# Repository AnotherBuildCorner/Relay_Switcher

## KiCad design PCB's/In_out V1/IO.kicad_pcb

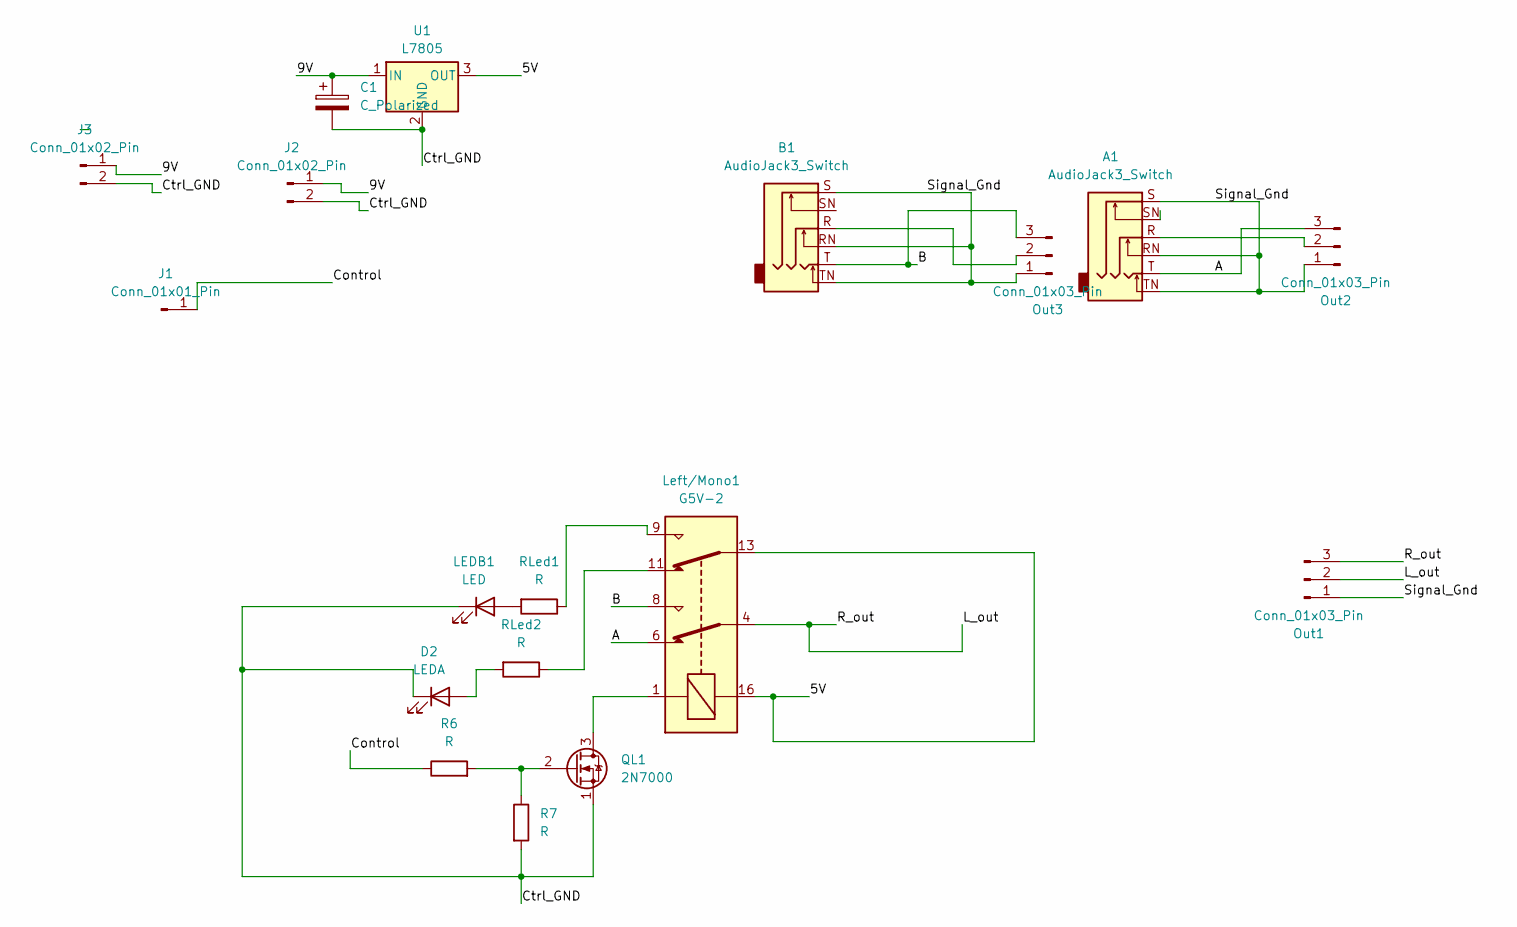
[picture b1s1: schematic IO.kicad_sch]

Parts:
A1: AudioJack3_Switch; Jack_6.35mm_Neutrik_NMJ6HFD3_Horizontal
B1: AudioJack3_Switch; Jack_6.35mm_Neutrik_NMJ6HFD3_Horizontal
C1: C_Polarized; CP_Radial_D10.0mm_P3.50mm
D2: LEDA; LED_D5.0mm
J1: Conn_01x01_Pin; PinHeader_1x01_P2.54mm_Vertical
J2, J3: Conn_01x02_Pin; PinHeader_2x01_P2.54mm_Vertical
LEDB1: LED; LED_D5.0mm
Left/Mono1: G5V-2; Relay_DPDT_Omron_G5V-2
Out1, Out2, Out3: Conn_01x03_Pin; PinHeader_1x03_P2.54mm_Vertical
QL1: 2N7000; TO-92_Inline
R6, R7: R; R_Axial_DIN0207_L6.3mm_D2.5mm_P10.16mm_Horizontal
RLed1, RLed2: R; R_Axial_DIN0207_L6.3mm_D2.5mm_P10.16mm_Horizontal
U1: L7805; TO-220-3_Vertical

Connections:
/5V: Left/Mono1.13, Left/Mono1.16, U1.3 (OUT)
/9V: C1.1, J2.1, J3.1, U1.1 (IN)
/A: A1.T, Left/Mono1.6, Out2.3
/B: B1.T, Left/Mono1.8, Out3.3
/Control: J1.1, R6.1
/Ctrl_GND: C1.2, D2.1 (K), J2.2, J3.2, LEDB1.1 (K), QL1.1 (S), R7.2, U1.2 (GND)
/L_out: Left/Mono1.4, Out1.2, Out1.3
/Signal_Gnd: A1.RN, A1.S, A1.TN, B1.RN, B1.S, B1.TN, Out1.1, Out2.1, Out3.1
unnamed: D2.2 (A), RLed2.2
unnamed: LEDB1.2 (A), RLed1.2
unnamed: Left/Mono1.9, RLed1.1
unnamed: Left/Mono1.11, RLed2.1
unnamed: A1.R, Out2.2
unnamed: B1.R, Out3.2
unnamed: Left/Mono1.1, QL1.3 (D)
unnamed: QL1.2 (G), R6.2, R7.1

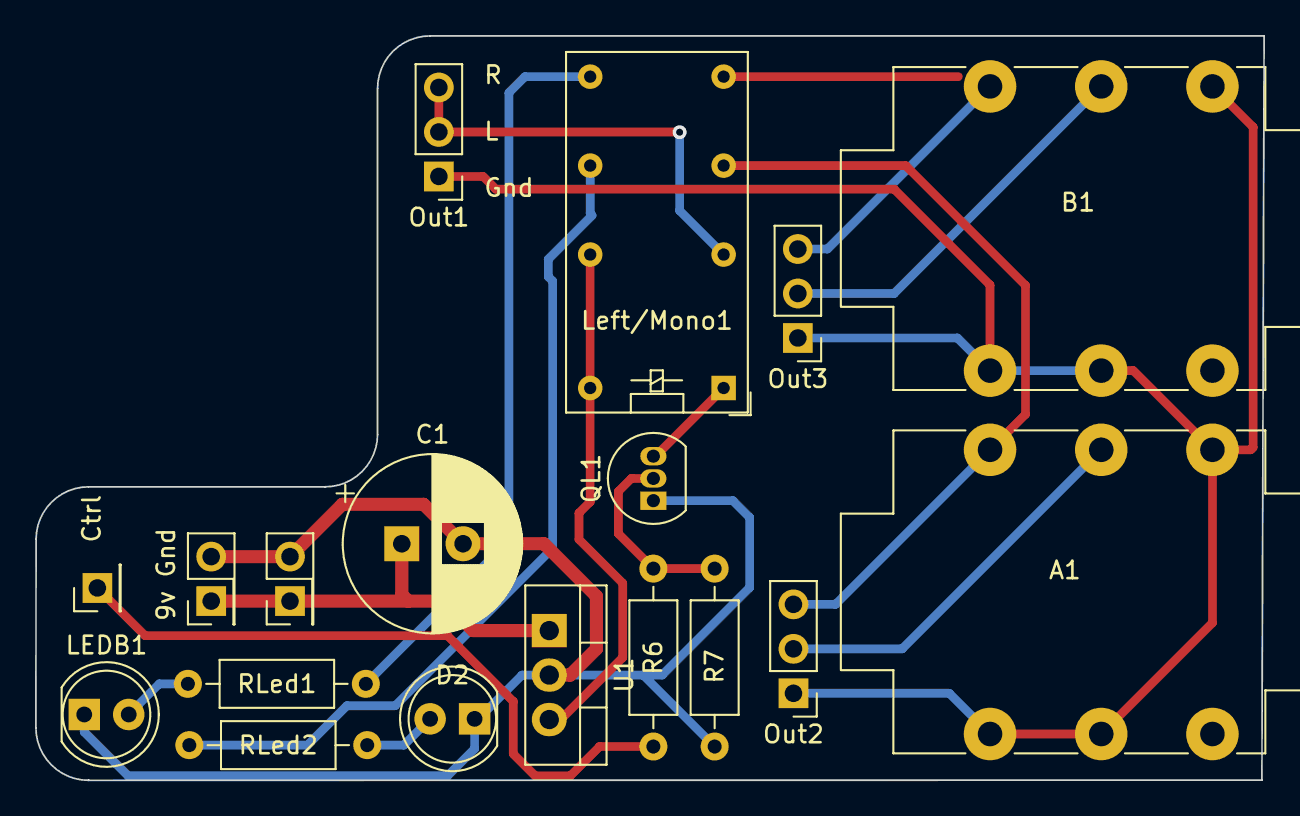
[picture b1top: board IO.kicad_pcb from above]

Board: 2 copper layers, 70.1 x 42.5 mm, 18 parts (0 on the bottom side), 16 nets.

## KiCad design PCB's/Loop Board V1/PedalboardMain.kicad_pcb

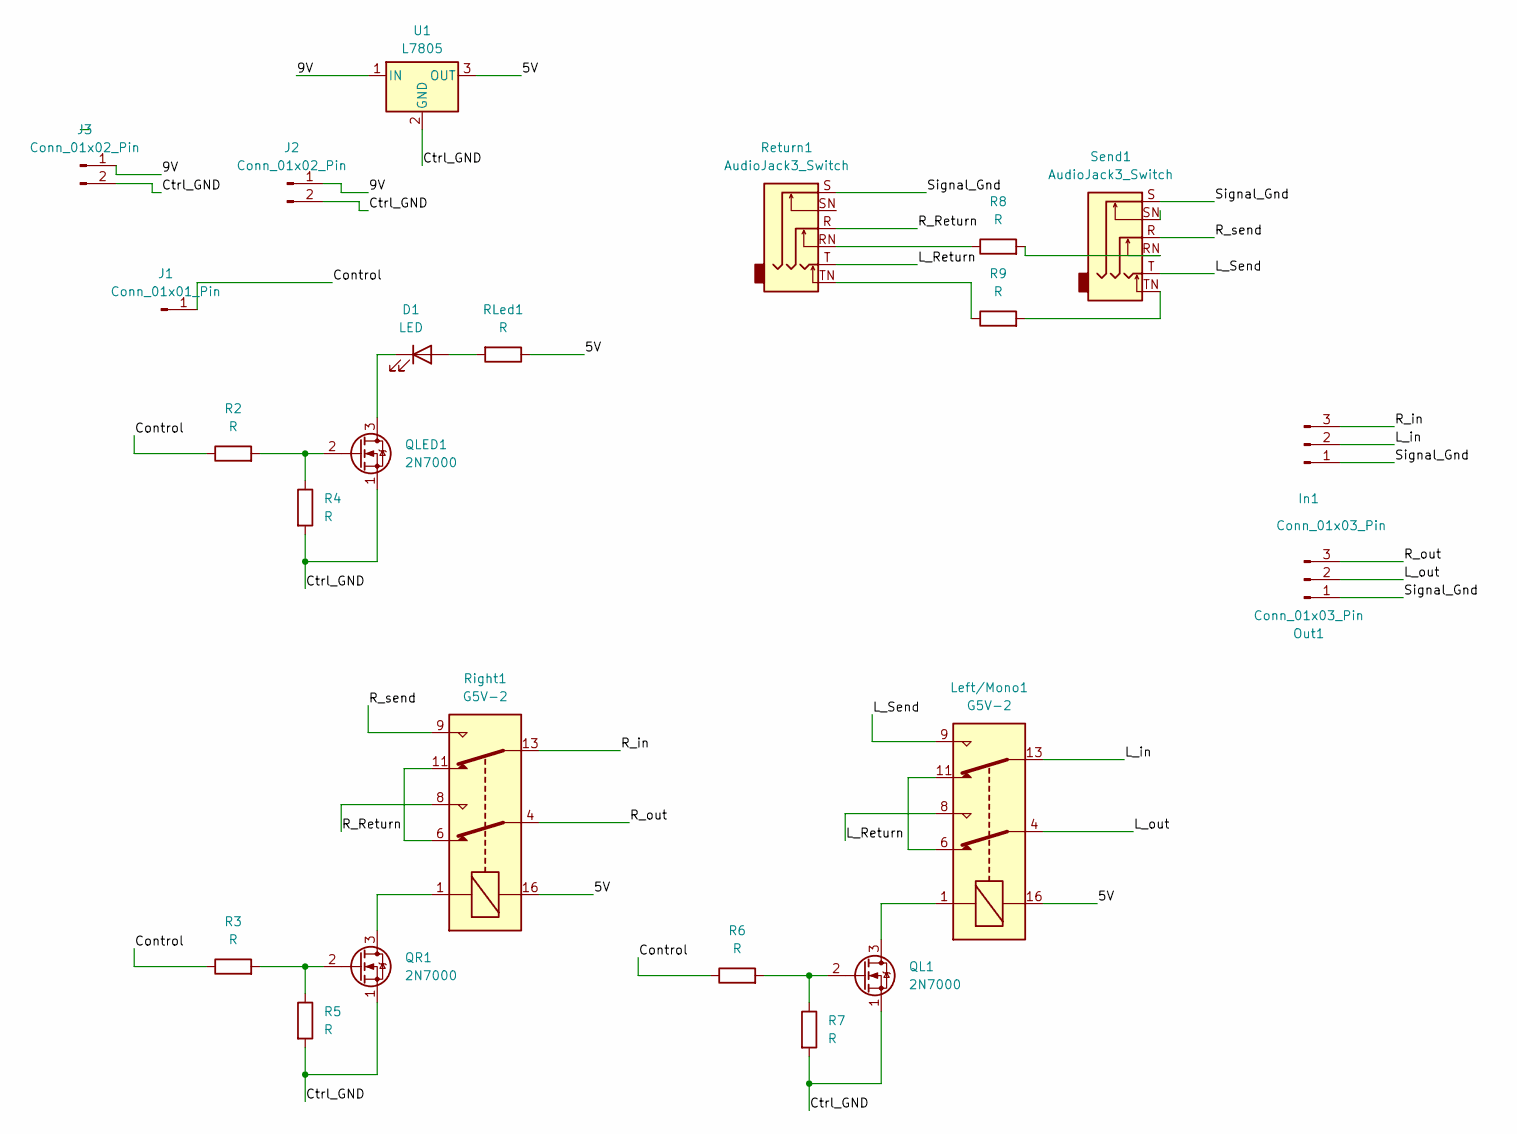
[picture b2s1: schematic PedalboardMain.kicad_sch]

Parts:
D1: LED; LED_D5.0mm
In1: Conn_01x03_Pin; PinHeader_1x03_P2.54mm_Vertical
J1: Conn_01x01_Pin; PinHeader_1x01_P2.54mm_Vertical
J2, J3: Conn_01x02_Pin; PinHeader_2x01_P2.54mm_Vertical
Left/Mono1: G5V-2; Relay_DPDT_Omron_G5V-2
Out1: Conn_01x03_Pin; PinHeader_1x03_P2.54mm_Vertical
QL1: 2N7000; TO-92_Inline
QLED1: 2N7000; TO-92_Inline
QR1: 2N7000; TO-92_Inline
R2, R3, R4, R5, R6, R7: R; R_Axial_DIN0207_L6.3mm_D2.5mm_P10.16mm_Horizontal
R8, R9: R; R_0201_0603Metric
RLed1: R; R_Axial_DIN0207_L6.3mm_D2.5mm_P10.16mm_Horizontal
Return1: AudioJack3_Switch; Jack_6.35mm_Neutrik_NMJ6HFD3_Horizontal
Right1: G5V-2; Relay_DPDT_Omron_G5V-2
Send1: AudioJack3_Switch; Jack_6.35mm_Neutrik_NMJ6HFD3_Horizontal
U1: L7805; TO-220-3_Vertical

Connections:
/5V: Left/Mono1.16, RLed1.1, Right1.16, U1.3 (OUT)
/9V: J2.1, J3.1, U1.1 (IN)
/Control: J1.1, R2.1, R3.1, R6.1
/Ctrl_GND: J2.2, J3.2, QL1.1 (S), QLED1.1 (S), QR1.1 (S), R4.2, R5.2, R7.2, U1.2 (GND)
/L_Return: Left/Mono1.8, Return1.T
/L_Send: Left/Mono1.9, Send1.T
/L_in: In1.2, Left/Mono1.13
/L_out: Left/Mono1.4, Out1.2
/R_Return: Return1.R, Right1.8
/R_in: In1.3, Right1.13
/R_out: Out1.3, Right1.4
/R_send: Right1.9, Send1.R
/Signal_Gnd: In1.1, Out1.1, Return1.S, Send1.S
unnamed: D1.2 (A), RLed1.2
unnamed: D1.1 (K), QLED1.3 (D)
unnamed: Left/Mono1.6, Left/Mono1.11
unnamed: Left/Mono1.1, QL1.3 (D)
unnamed: QL1.2 (G), R6.2, R7.1
unnamed: QLED1.2 (G), R2.2, R4.1
unnamed: QR1.3 (D), Right1.1
unnamed: QR1.2 (G), R3.2, R5.1
unnamed: R8.1, Return1.RN
unnamed: R8.2, Send1.RN
unnamed: R9.1, Return1.TN
unnamed: R9.2, Send1.TN
unnamed: Right1.6, Right1.11

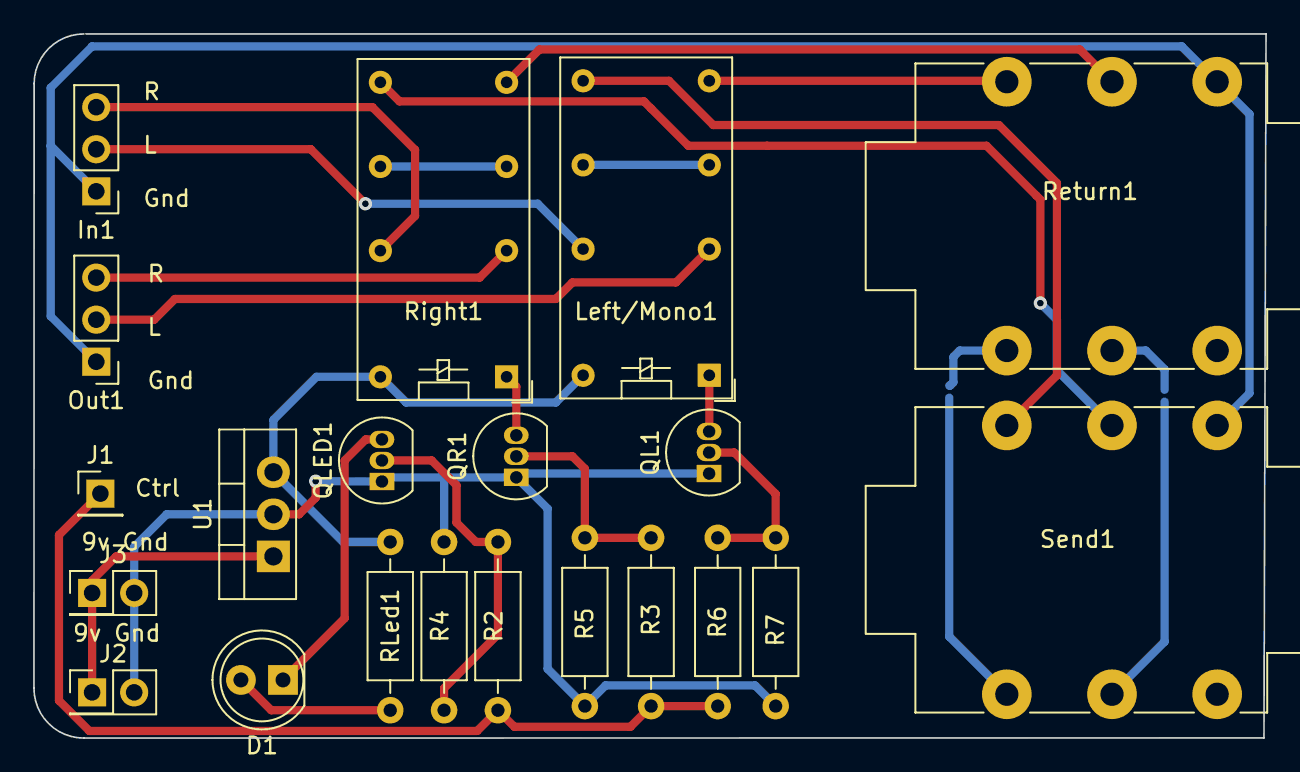
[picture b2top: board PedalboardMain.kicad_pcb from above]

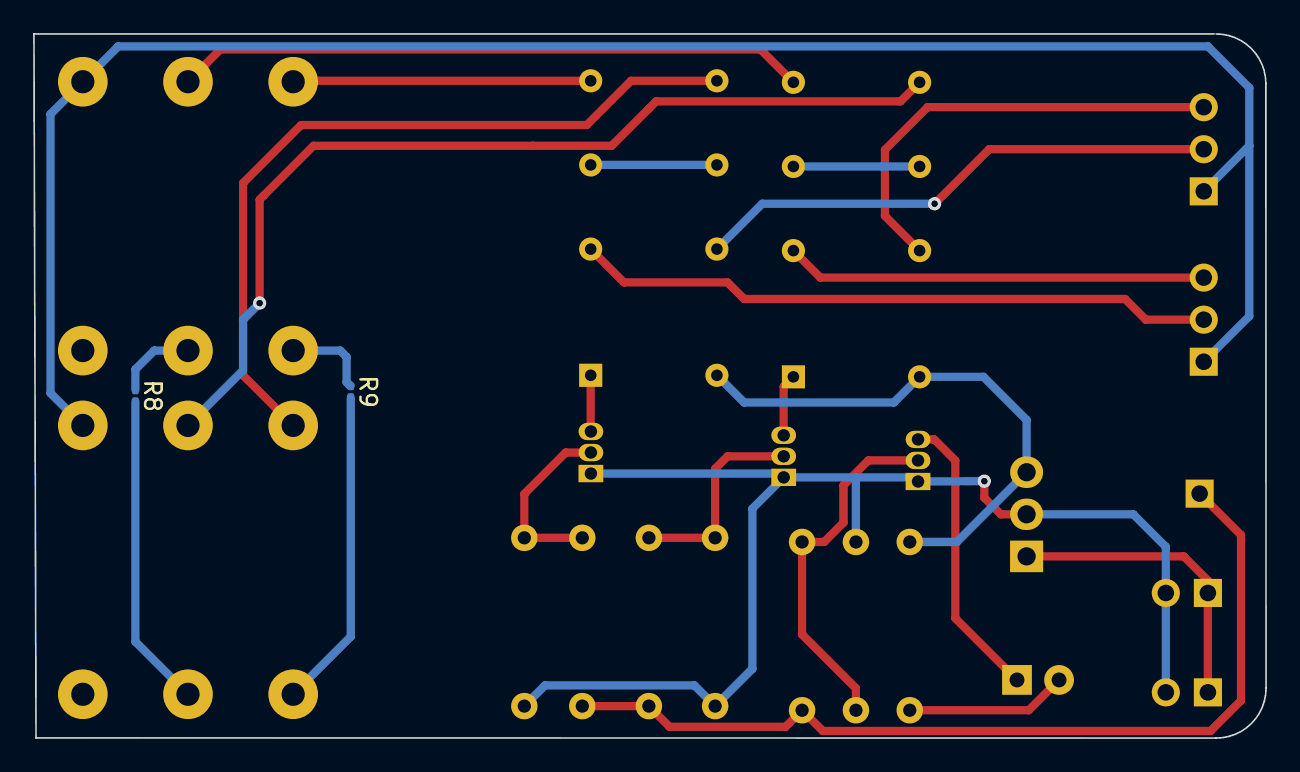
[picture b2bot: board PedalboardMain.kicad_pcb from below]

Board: 2 copper layers, 74.4 x 42.5 mm, 23 parts (2 on the bottom side), 26 nets.

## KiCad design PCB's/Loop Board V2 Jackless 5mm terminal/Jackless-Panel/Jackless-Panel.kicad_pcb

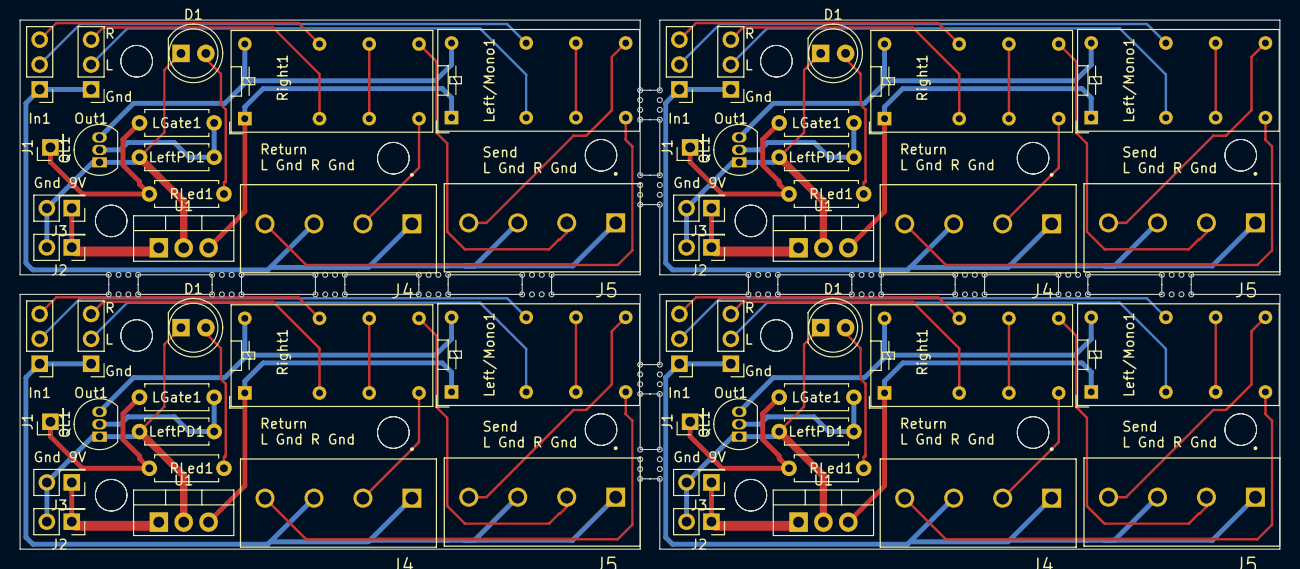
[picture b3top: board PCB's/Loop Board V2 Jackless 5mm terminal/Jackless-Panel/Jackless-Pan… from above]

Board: 2 copper layers, 128.6 x 54.0 mm, 172 parts (0 on the bottom side), 72 nets.

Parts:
D1, D1#2, D1#3, D1#4: LED; LED_D5.0mm
In1, In1#2, In1#3, In1#4: Conn_01x03_Pin; PinHeader_1x03_P2.54mm_Vertical
J1, J1#2, J1#3, J1#4: Conn_01x01_Pin; PinHeader_1x01_P2.54mm_Vertical
J2, J2#2, J2#3, J2#4, J3, J3#2, J3#3, J3#4: Conn_01x02_Pin; PinHeader_2x01_P2.54mm_Vertical
J4, J4#2, J4#3, J4#4, J5, J5#2, J5#3, J5#4: Screw_Terminal_01x04; CUI_TB001-500-04BE
KiKit_MB_1_1, KiKit_MB_1_2, KiKit_MB_1_3, KiKit_MB_1_4, KiKit_MB_2_1, KiKit_MB_2_2, KiKit_MB_2_3, KiKit_MB_2_4, KiKit_MB_3_1, KiKit_MB_3_2, KiKit_MB_3_3, KiKit_MB_3_4, KiKit_MB_4_1, KiKit_MB_4_2, KiKit_MB_4_3, KiKit_MB_4_4, KiKit_MB_5_1, KiKit_MB_5_2, KiKit_MB_5_3, KiKit_MB_5_4, KiKit_MB_6_1, KiKit_MB_6_2, KiKit_MB_6_3, KiKit_MB_6_4, KiKit_MB_7_1, KiKit_MB_7_2, KiKit_MB_7_3, KiKit_MB_7_4, KiKit_MB_8_1, KiKit_MB_8_2, KiKit_MB_8_3, KiKit_MB_8_4, KiKit_MB_9_1, KiKit_MB_9_2, KiKit_MB_9_3, KiKit_MB_9_4, KiKit_MB_10_1, KiKit_MB_10_2, KiKit_MB_10_3, KiKit_MB_10_4, KiKit_MB_11_1, KiKit_MB_11_2, KiKit_MB_11_3, KiKit_MB_11_4, KiKit_MB_12_1, KiKit_MB_12_2, KiKit_MB_12_3, KiKit_MB_12_4, KiKit_MB_13_1, KiKit_MB_13_2, KiKit_MB_13_3, KiKit_MB_13_4, KiKit_MB_14_1, KiKit_MB_14_2, KiKit_MB_14_3, KiKit_MB_14_4, KiKit_MB_15_1, KiKit_MB_15_2, KiKit_MB_15_3, KiKit_MB_15_4, KiKit_MB_16_1, KiKit_MB_16_2, KiKit_MB_16_3, KiKit_MB_16_4, KiKit_MB_17_1, KiKit_MB_17_2, KiKit_MB_17_3, KiKit_MB_17_4, KiKit_MB_18_1, KiKit_MB_18_2, KiKit_MB_18_3, KiKit_MB_18_4, KiKit_MB_19_1, KiKit_MB_19_2, KiKit_MB_19_3, KiKit_MB_19_4, KiKit_MB_20_1, KiKit_MB_20_2, KiKit_MB_20_3, KiKit_MB_20_4, KiKit_MB_21_1, KiKit_MB_21_2, KiKit_MB_21_3, KiKit_MB_21_4, KiKit_MB_22_1, KiKit_MB_22_2, KiKit_MB_22_3, KiKit_MB_22_4, KiKit_MB_23_1, KiKit_MB_23_2, KiKit_MB_23_3, KiKit_MB_23_4, KiKit_MB_24_1, KiKit_MB_24_2, KiKit_MB_24_3, KiKit_MB_24_4, KiKit_MB_25_1, KiKit_MB_25_2, KiKit_MB_25_3, KiKit_MB_25_4, KiKit_MB_26_1, KiKit_MB_26_2, KiKit_MB_26_3, KiKit_MB_26_4, KiKit_MB_27_1, KiKit_MB_27_2, KiKit_MB_27_3, KiKit_MB_27_4, KiKit_MB_28_1, KiKit_MB_28_2, KiKit_MB_28_3, KiKit_MB_28_4: NPTH
LGate1, LGate1#2, LGate1#3, LGate1#4: R; R_Axial_DIN0207_L6.3mm_D2.5mm_P7.62mm_Horizontal
Left/Mono1, Left/Mono1#2, Left/Mono1#3, Left/Mono1#4: G5V-2; Relay_DPDT_Omron_G5V-2
LeftPD1, LeftPD1#2, LeftPD1#3, LeftPD1#4: R; R_Axial_DIN0207_L6.3mm_D2.5mm_P7.62mm_Horizontal
Out1, Out1#2, Out1#3, Out1#4: Conn_01x03_Pin; PinHeader_1x03_P2.54mm_Vertical
QL1, QL1#2, QL1#3, QL1#4: 2N7000; TO-92_Inline
RLed1, RLed1#2, RLed1#3, RLed1#4: 100; R_Axial_DIN0207_L6.3mm_D2.5mm_P7.62mm_Horizontal
Right1, Right1#2, Right1#3, Right1#4: G5V-2; Relay_DPDT_Omron_G5V-2
U1, U1#2, U1#3, U1#4: L7805; TO-220-3_Vertical

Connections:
Board_0-/5V: Left/Mono1#3.1, Right1.1, U1#2.3 (OUT)
Board_0-/9V: J2#2.1, J3#2.1, U1#2.1 (IN)
Board_0-/Control: J1#4.1, LGate1#4.1, RLed1#4.1
Board_0-/Ctrl_GND: D1#3.1 (K), J2#2.2, J3#2.2, LeftPD1#2.2, QL1#4.1 (S), U1#2.2 (GND)
Board_0-/L_Return: J4#3.4, Left/Mono1#3.8
Board_0-/L_Send: J5#4.4, Left/Mono1#3.9
Board_0-/L_in: In1#2.2, Left/Mono1#3.13
Board_0-/L_out: Left/Mono1#3.4, Out1.2
Board_0-/R_Return: J4#3.2, Right1.8
Board_0-/R_in: In1#2.3, Right1.13
Board_0-/R_out: Out1.3, Right1.4
Board_0-/R_send: J5#4.2, Right1.9
Board_0-/Signal_Gnd: In1#2.1, J4#3.1, J4#3.3, J5#4.1, J5#4.3, Out1.1
Board_0-Net-(D1-A): D1#3.2 (A), RLed1#4.2
Board_0-Net-(Left/Mono1-Pad11): Left/Mono1#3.6, Left/Mono1#3.11
Board_0-Net-(QL1-D): Left/Mono1#3.16, QL1#4.3 (D), Right1.16
Board_0-Net-(QL1-G): LGate1#4.2, LeftPD1#2.1, QL1#4.2 (G)
Board_0-Net-(Right1-Pad11): Right1.6, Right1.11
Board_1-/5V: Left/Mono1#2.1, Right1#2.1, U1.3 (OUT)
Board_1-/9V: J2#3.1, J3.1, U1.1 (IN)
Board_1-/Control: J1#3.1, LGate1#2.1, RLed1.1
Board_1-/Ctrl_GND: D1#2.1 (K), J2#3.2, J3.2, LeftPD1#3.2, QL1#2.1 (S), U1.2 (GND)
Board_1-/L_Return: J4#4.4, Left/Mono1#2.8
Board_1-/L_Send: J5.4, Left/Mono1#2.9
Board_1-/L_in: In1.2, Left/Mono1#2.13
Board_1-/L_out: Left/Mono1#2.4, Out1#2.2
Board_1-/R_Return: J4#4.2, Right1#2.8
Board_1-/R_in: In1.3, Right1#2.13
Board_1-/R_out: Out1#2.3, Right1#2.4
Board_1-/R_send: J5.2, Right1#2.9
Board_1-/Signal_Gnd: In1.1, J4#4.1, J4#4.3, J5.1, J5.3, Out1#2.1
Board_1-Net-(D1-A): D1#2.2 (A), RLed1.2
Board_1-Net-(Left/Mono1-Pad11): Left/Mono1#2.6, Left/Mono1#2.11
Board_1-Net-(QL1-D): Left/Mono1#2.16, QL1#2.3 (D), Right1#2.16
Board_1-Net-(QL1-G): LGate1#2.2, LeftPD1#3.1, QL1#2.2 (G)
Board_1-Net-(Right1-Pad11): Right1#2.6, Right1#2.11
Board_2-/5V: Left/Mono1.1, Right1#4.1, U1#3.3 (OUT)
Board_2-/9V: J2#4.1, J3#4.1, U1#3.1 (IN)
Board_2-/Control: J1#2.1, LGate1.1, RLed1#2.1
Board_2-/Ctrl_GND: D1.1 (K), J2#4.2, J3#4.2, LeftPD1#4.2, QL1#3.1 (S), U1#3.2 (GND)
Board_2-/L_Return: J4#2.4, Left/Mono1.8
Board_2-/L_Send: J5#2.4, Left/Mono1.9
Board_2-/L_in: In1#4.2, Left/Mono1.13
Board_2-/L_out: Left/Mono1.4, Out1#4.2
Board_2-/R_Return: J4#2.2, Right1#4.8
Board_2-/R_in: In1#4.3, Right1#4.13
Board_2-/R_out: Out1#4.3, Right1#4.4
Board_2-/R_send: J5#2.2, Right1#4.9
Board_2-/Signal_Gnd: In1#4.1, J4#2.1, J4#2.3, J5#2.1, J5#2.3, Out1#4.1
Board_2-Net-(D1-A): D1.2 (A), RLed1#2.2
Board_2-Net-(Left/Mono1-Pad11): Left/Mono1.6, Left/Mono1.11
Board_2-Net-(QL1-D): Left/Mono1.16, QL1#3.3 (D), Right1#4.16
Board_2-Net-(QL1-G): LGate1.2, LeftPD1#4.1, QL1#3.2 (G)
Board_2-Net-(Right1-Pad11): Right1#4.6, Right1#4.11
Board_3-/5V: Left/Mono1#4.1, Right1#3.1, U1#4.3 (OUT)
Board_3-/9V: J2.1, J3#3.1, U1#4.1 (IN)
Board_3-/Control: J1.1, LGate1#3.1, RLed1#3.1
Board_3-/Ctrl_GND: D1#4.1 (K), J2.2, J3#3.2, LeftPD1.2, QL1.1 (S), U1#4.2 (GND)
Board_3-/L_Return: J4.4, Left/Mono1#4.8
Board_3-/L_Send: J5#3.4, Left/Mono1#4.9
Board_3-/L_in: In1#3.2, Left/Mono1#4.13
Board_3-/L_out: Left/Mono1#4.4, Out1#3.2
Board_3-/R_Return: J4.2, Right1#3.8
Board_3-/R_in: In1#3.3, Right1#3.13
Board_3-/R_out: Out1#3.3, Right1#3.4
Board_3-/R_send: J5#3.2, Right1#3.9
Board_3-/Signal_Gnd: In1#3.1, J4.1, J4.3, J5#3.1, J5#3.3, Out1#3.1
Board_3-Net-(D1-A): D1#4.2 (A), RLed1#3.2
Board_3-Net-(Left/Mono1-Pad11): Left/Mono1#4.6, Left/Mono1#4.11
Board_3-Net-(QL1-D): Left/Mono1#4.16, QL1.3 (D), Right1#3.16
Board_3-Net-(QL1-G): LGate1#3.2, LeftPD1.1, QL1.2 (G)
Board_3-Net-(Right1-Pad11): Right1#3.6, Right1#3.11

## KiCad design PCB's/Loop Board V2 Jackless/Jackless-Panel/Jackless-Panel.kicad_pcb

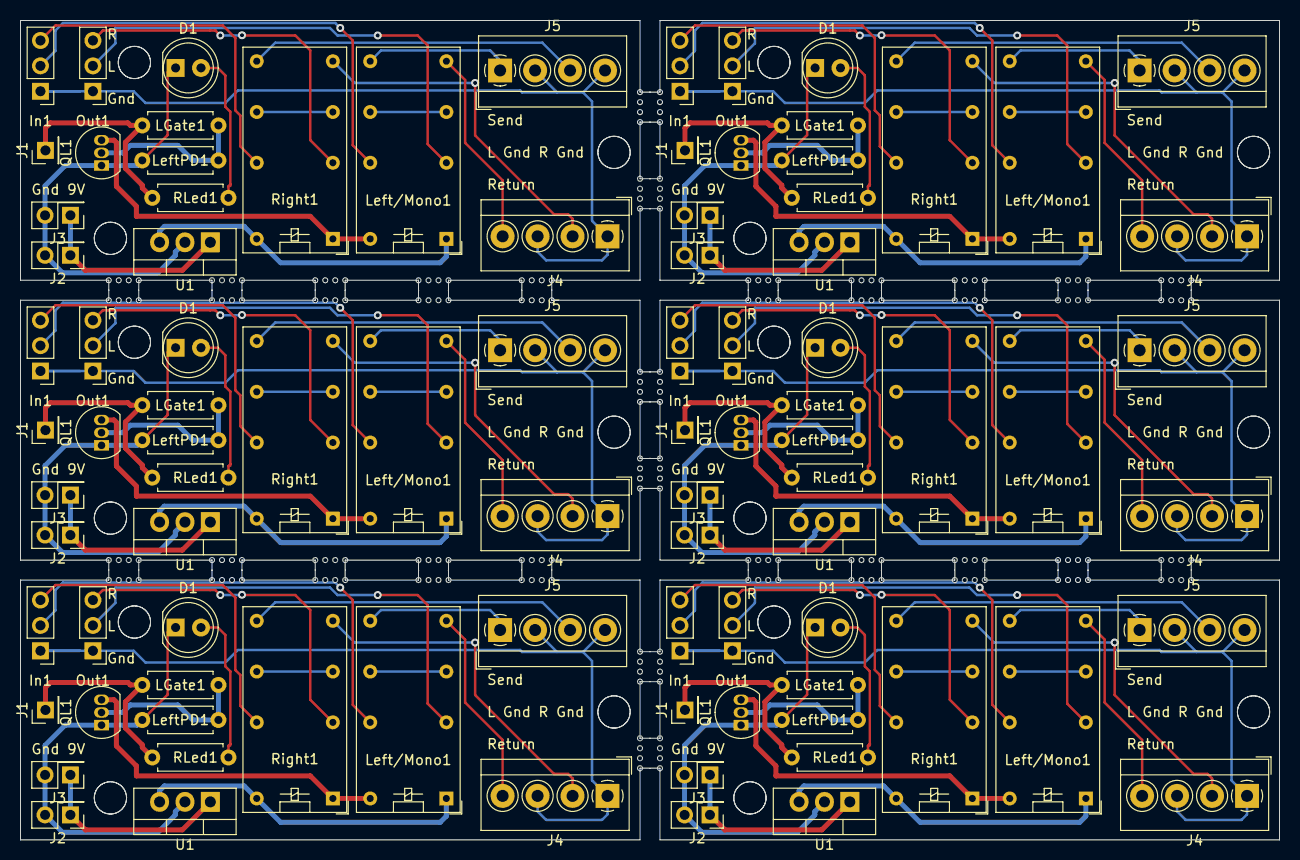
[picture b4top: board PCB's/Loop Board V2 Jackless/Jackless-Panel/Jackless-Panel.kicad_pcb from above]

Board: 2 copper layers, 126.0 x 82.0 mm, 298 parts (0 on the bottom side), 108 nets.

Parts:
D1, D1#2, D1#3, D1#4, D1#5, D1#6: LED; LED_D5.0mm
In1, In1#2, In1#3, In1#4, In1#5, In1#6: Conn_01x03_Pin; PinHeader_1x03_P2.54mm_Vertical
J1, J1#2, J1#3, J1#4, J1#5, J1#6: Conn_01x01_Pin; PinHeader_1x01_P2.54mm_Vertical
J2, J2#2, J2#3, J2#4, J2#5, J2#6, J3, J3#2, J3#3, J3#4, J3#5, J3#6: Conn_01x02_Pin; PinHeader_2x01_P2.54mm_Vertical
J4, J4#2, J4#3, J4#4, J4#5, J4#6, J5, J5#2, J5#3, J5#4, J5#5, J5#6: Screw_Terminal_01x04; TerminalBlock_4Ucon_1x04_P3.50mm_Horizontal
KiKit_MB_1_1, KiKit_MB_1_2, KiKit_MB_1_3, KiKit_MB_1_4, KiKit_MB_2_1, KiKit_MB_2_2, KiKit_MB_2_3, KiKit_MB_2_4, KiKit_MB_3_1, KiKit_MB_3_2, KiKit_MB_3_3, KiKit_MB_3_4, KiKit_MB_4_1, KiKit_MB_4_2, KiKit_MB_4_3, KiKit_MB_4_4, KiKit_MB_5_1, KiKit_MB_5_2, KiKit_MB_5_3, KiKit_MB_5_4, KiKit_MB_6_1, KiKit_MB_6_2, KiKit_MB_6_3, KiKit_MB_6_4, KiKit_MB_7_1, KiKit_MB_7_2, KiKit_MB_7_3, KiKit_MB_7_4, KiKit_MB_8_1, KiKit_MB_8_2, KiKit_MB_8_3, KiKit_MB_8_4, KiKit_MB_9_1, KiKit_MB_9_2, KiKit_MB_9_3, KiKit_MB_9_4, KiKit_MB_10_1, KiKit_MB_10_2, KiKit_MB_10_3, KiKit_MB_10_4, KiKit_MB_11_1, KiKit_MB_11_2, KiKit_MB_11_3, KiKit_MB_11_4, KiKit_MB_12_1, KiKit_MB_12_2, KiKit_MB_12_3, KiKit_MB_12_4, KiKit_MB_13_1, KiKit_MB_13_2, KiKit_MB_13_3, KiKit_MB_13_4, KiKit_MB_14_1, KiKit_MB_14_2, KiKit_MB_14_3, KiKit_MB_14_4, KiKit_MB_15_1, KiKit_MB_15_2, KiKit_MB_15_3, KiKit_MB_15_4, KiKit_MB_16_1, KiKit_MB_16_2, KiKit_MB_16_3, KiKit_MB_16_4, KiKit_MB_17_1, KiKit_MB_17_2, KiKit_MB_17_3, KiKit_MB_17_4, KiKit_MB_18_1, KiKit_MB_18_2, KiKit_MB_18_3, KiKit_MB_18_4, KiKit_MB_19_1, KiKit_MB_19_2, KiKit_MB_19_3, KiKit_MB_19_4, KiKit_MB_20_1, KiKit_MB_20_2, KiKit_MB_20_3, KiKit_MB_20_4, KiKit_MB_21_1, KiKit_MB_21_2, KiKit_MB_21_3, KiKit_MB_21_4, KiKit_MB_22_1, KiKit_MB_22_2, KiKit_MB_22_3, KiKit_MB_22_4, KiKit_MB_23_1, KiKit_MB_23_2, KiKit_MB_23_3, KiKit_MB_23_4, KiKit_MB_24_1, KiKit_MB_24_2, KiKit_MB_24_3, KiKit_MB_24_4, KiKit_MB_25_1, KiKit_MB_25_2, KiKit_MB_25_3, KiKit_MB_25_4, KiKit_MB_26_1, KiKit_MB_26_2, KiKit_MB_26_3, KiKit_MB_26_4, KiKit_MB_27_1, KiKit_MB_27_2, KiKit_MB_27_3, KiKit_MB_27_4, KiKit_MB_28_1, KiKit_MB_28_2, KiKit_MB_28_3, KiKit_MB_28_4, KiKit_MB_29_1, KiKit_MB_29_2, KiKit_MB_29_3, KiKit_MB_29_4, KiKit_MB_30_1, KiKit_MB_30_2, KiKit_MB_30_3, KiKit_MB_30_4, KiKit_MB_31_1, KiKit_MB_31_2, KiKit_MB_31_3, KiKit_MB_31_4, KiKit_MB_32_1, KiKit_MB_32_2, KiKit_MB_32_3, KiKit_MB_32_4, KiKit_MB_33_1, KiKit_MB_33_2, KiKit_MB_33_3, KiKit_MB_33_4, KiKit_MB_34_1, KiKit_MB_34_2, KiKit_MB_34_3, KiKit_MB_34_4, KiKit_MB_35_1, KiKit_MB_35_2, KiKit_MB_35_3, KiKit_MB_35_4, KiKit_MB_36_1, KiKit_MB_36_2, KiKit_MB_36_3, KiKit_MB_36_4, KiKit_MB_37_1, KiKit_MB_37_2, KiKit_MB_37_3, KiKit_MB_37_4, KiKit_MB_38_1, KiKit_MB_38_2, KiKit_MB_38_3, KiKit_MB_38_4, KiKit_MB_39_1, KiKit_MB_39_2, KiKit_MB_39_3, KiKit_MB_39_4, KiKit_MB_40_1, KiKit_MB_40_2, KiKit_MB_40_3, KiKit_MB_40_4, KiKit_MB_41_1, KiKit_MB_41_2, KiKit_MB_41_3, KiKit_MB_41_4, KiKit_MB_42_1, KiKit_MB_42_2, KiKit_MB_42_3, KiKit_MB_42_4, KiKit_MB_43_1, KiKit_MB_43_2, KiKit_MB_43_3, KiKit_MB_43_4, KiKit_MB_44_1, KiKit_MB_44_2, KiKit_MB_44_3, KiKit_MB_44_4, KiKit_MB_45_1, KiKit_MB_45_2, KiKit_MB_45_3, KiKit_MB_45_4, KiKit_MB_46_1, KiKit_MB_46_2, KiKit_MB_46_3, KiKit_MB_46_4, KiKit_MB_47_1, KiKit_MB_47_2, KiKit_MB_47_3, KiKit_MB_47_4, KiKit_MB_48_1, KiKit_MB_48_2, KiKit_MB_48_3, KiKit_MB_48_4, KiKit_MB_49_1, KiKit_MB_49_2, KiKit_MB_49_3, KiKit_MB_49_4, KiKit_MB_50_1, KiKit_MB_50_2, KiKit_MB_50_3, KiKit_MB_50_4, KiKit_MB_51_1, KiKit_MB_51_2, KiKit_MB_51_3, KiKit_MB_51_4, KiKit_MB_52_1, KiKit_MB_52_2, KiKit_MB_52_3, KiKit_MB_52_4: NPTH
LGate1, LGate1#2, LGate1#3, LGate1#4, LGate1#5, LGate1#6: R; R_Axial_DIN0207_L6.3mm_D2.5mm_P7.62mm_Horizontal
Left/Mono1, Left/Mono1#2, Left/Mono1#3, Left/Mono1#4, Left/Mono1#5, Left/Mono1#6: G5V-2; Relay_DPDT_Omron_G5V-2
LeftPD1, LeftPD1#2, LeftPD1#3, LeftPD1#4, LeftPD1#5, LeftPD1#6: R; R_Axial_DIN0207_L6.3mm_D2.5mm_P7.62mm_Horizontal
Out1, Out1#2, Out1#3, Out1#4, Out1#5, Out1#6: Conn_01x03_Pin; PinHeader_1x03_P2.54mm_Vertical
QL1, QL1#2, QL1#3, QL1#4, QL1#5, QL1#6: 2N7000; TO-92_Inline
RLed1, RLed1#2, RLed1#3, RLed1#4, RLed1#5, RLed1#6: 100; R_Axial_DIN0207_L6.3mm_D2.5mm_P7.62mm_Horizontal
Right1, Right1#2, Right1#3, Right1#4, Right1#5, Right1#6: G5V-2; Relay_DPDT_Omron_G5V-2
U1, U1#2, U1#3, U1#4, U1#5, U1#6: L7805; TO-220-3_Vertical

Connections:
Board_0-/5V: Left/Mono1#4.1, Right1#3.16, U1#5.3 (OUT)
Board_0-/9V: J2.1, J3#5.1, U1#5.1 (IN)
Board_0-/Control: J1.1, LGate1#4.1, RLed1#2.1
Board_0-/Ctrl_GND: D1#3.1 (K), J2.2, J3#5.2, LeftPD1#6.2, QL1#6.1 (S), U1#5.2 (GND)
Board_0-/L_Return: J4#3.4, Left/Mono1#4.8
Board_0-/L_Send: J5#5.1, Left/Mono1#4.9
Board_0-/L_in: In1#3.2, Left/Mono1#4.13
Board_0-/L_out: Left/Mono1#4.4, Out1#6.2
Board_0-/R_Return: J4#3.2, Right1#3.8
Board_0-/R_in: In1#3.3, Right1#3.13
Board_0-/R_out: Out1#6.3, Right1#3.4
Board_0-/R_send: J5#5.3, Right1#3.9
Board_0-/Signal_Gnd: In1#3.1, J4#3.1, J4#3.3, J5#5.2, J5#5.4, Out1#6.1
Board_0-Net-(D1-A): D1#3.2 (A), RLed1#2.2
Board_0-Net-(Left/Mono1-Pad11): Left/Mono1#4.6, Left/Mono1#4.11
Board_0-Net-(QL1-D): Left/Mono1#4.16, QL1#6.3 (D), Right1#3.1
Board_0-Net-(QL1-G): LGate1#4.2, LeftPD1#6.1, QL1#6.2 (G)
Board_0-Net-(Right1-Pad11): Right1#3.6, Right1#3.11
Board_1-/5V: Left/Mono1#6.1, Right1#5.16, U1#6.3 (OUT)
Board_1-/9V: J2#6.1, J3#2.1, U1#6.1 (IN)
Board_1-/Control: J1#2.1, LGate1#3.1, RLed1#4.1
Board_1-/Ctrl_GND: D1#4.1 (K), J2#6.2, J3#2.2, LeftPD1#3.2, QL1#2.1 (S), U1#6.2 (GND)
Board_1-/L_Return: J4#5.4, Left/Mono1#6.8
Board_1-/L_Send: J5#4.1, Left/Mono1#6.9
Board_1-/L_in: In1#4.2, Left/Mono1#6.13
Board_1-/L_out: Left/Mono1#6.4, Out1#2.2
Board_1-/R_Return: J4#5.2, Right1#5.8
Board_1-/R_in: In1#4.3, Right1#5.13
Board_1-/R_out: Out1#2.3, Right1#5.4
Board_1-/R_send: J5#4.3, Right1#5.9
Board_1-/Signal_Gnd: In1#4.1, J4#5.1, J4#5.3, J5#4.2, J5#4.4, Out1#2.1
Board_1-Net-(D1-A): D1#4.2 (A), RLed1#4.2
Board_1-Net-(Left/Mono1-Pad11): Left/Mono1#6.6, Left/Mono1#6.11
Board_1-Net-(QL1-D): Left/Mono1#6.16, QL1#2.3 (D), Right1#5.1
Board_1-Net-(QL1-G): LGate1#3.2, LeftPD1#3.1, QL1#2.2 (G)
Board_1-Net-(Right1-Pad11): Right1#5.6, Right1#5.11
Board_2-/5V: Left/Mono1#5.1, Right1#2.16, U1.3 (OUT)
Board_2-/9V: J2#5.1, J3.1, U1.1 (IN)
Board_2-/Control: J1#6.1, LGate1.1, RLed1.1
Board_2-/Ctrl_GND: D1#5.1 (K), J2#5.2, J3.2, LeftPD1#4.2, QL1#5.1 (S), U1.2 (GND)
Board_2-/L_Return: J4#2.4, Left/Mono1#5.8
Board_2-/L_Send: J5.1, Left/Mono1#5.9
Board_2-/L_in: In1#6.2, Left/Mono1#5.13
Board_2-/L_out: Left/Mono1#5.4, Out1.2
Board_2-/R_Return: J4#2.2, Right1#2.8
Board_2-/R_in: In1#6.3, Right1#2.13
Board_2-/R_out: Out1.3, Right1#2.4
Board_2-/R_send: J5.3, Right1#2.9
Board_2-/Signal_Gnd: In1#6.1, J4#2.1, J4#2.3, J5.2, J5.4, Out1.1
Board_2-Net-(D1-A): D1#5.2 (A), RLed1.2
Board_2-Net-(Left/Mono1-Pad11): Left/Mono1#5.6, Left/Mono1#5.11
Board_2-Net-(QL1-D): Left/Mono1#5.16, QL1#5.3 (D), Right1#2.1
Board_2-Net-(QL1-G): LGate1.2, LeftPD1#4.1, QL1#5.2 (G)
Board_2-Net-(Right1-Pad11): Right1#2.6, Right1#2.11
Board_3-/5V: Left/Mono1#2.1, Right1.16, U1#4.3 (OUT)
Board_3-/9V: J2#3.1, J3#3.1, U1#4.1 (IN)
Board_3-/Control: J1#5.1, LGate1#5.1, RLed1#5.1
Board_3-/Ctrl_GND: D1#6.1 (K), J2#3.2, J3#3.2, LeftPD1#5.2, QL1#3.1 (S), U1#4.2 (GND)
Board_3-/L_Return: J4.4, Left/Mono1#2.8
Board_3-/L_Send: J5#3.1, Left/Mono1#2.9
Board_3-/L_in: In1.2, Left/Mono1#2.13
Board_3-/L_out: Left/Mono1#2.4, Out1#5.2
Board_3-/R_Return: J4.2, Right1.8
Board_3-/R_in: In1.3, Right1.13
Board_3-/R_out: Out1#5.3, Right1.4
Board_3-/R_send: J5#3.3, Right1.9
Board_3-/Signal_Gnd: In1.1, J4.1, J4.3, J5#3.2, J5#3.4, Out1#5.1
Board_3-Net-(D1-A): D1#6.2 (A), RLed1#5.2
Board_3-Net-(Left/Mono1-Pad11): Left/Mono1#2.6, Left/Mono1#2.11
Board_3-Net-(QL1-D): Left/Mono1#2.16, QL1#3.3 (D), Right1.1
Board_3-Net-(QL1-G): LGate1#5.2, LeftPD1#5.1, QL1#3.2 (G)
Board_3-Net-(Right1-Pad11): Right1.6, Right1.11
Board_4-/5V: Left/Mono1#3.1, Right1#6.16, U1#3.3 (OUT)
Board_4-/9V: J2#4.1, J3#6.1, U1#3.1 (IN)
Board_4-/Control: J1#3.1, LGate1#2.1, RLed1#3.1
Board_4-/Ctrl_GND: D1.1 (K), J2#4.2, J3#6.2, LeftPD1.2, QL1.1 (S), U1#3.2 (GND)
Board_4-/L_Return: J4#4.4, Left/Mono1#3.8
Board_4-/L_Send: J5#2.1, Left/Mono1#3.9
Board_4-/L_in: In1#5.2, Left/Mono1#3.13
Board_4-/L_out: Left/Mono1#3.4, Out1#3.2
Board_4-/R_Return: J4#4.2, Right1#6.8
Board_4-/R_in: In1#5.3, Right1#6.13
Board_4-/R_out: Out1#3.3, Right1#6.4
Board_4-/R_send: J5#2.3, Right1#6.9
Board_4-/Signal_Gnd: In1#5.1, J4#4.1, J4#4.3, J5#2.2, J5#2.4, Out1#3.1
Board_4-Net-(D1-A): D1.2 (A), RLed1#3.2
Board_4-Net-(Left/Mono1-Pad11): Left/Mono1#3.6, Left/Mono1#3.11
Board_4-Net-(QL1-D): Left/Mono1#3.16, QL1.3 (D), Right1#6.1
Board_4-Net-(QL1-G): LGate1#2.2, LeftPD1.1, QL1.2 (G)
Board_4-Net-(Right1-Pad11): Right1#6.6, Right1#6.11
Board_5-/5V: Left/Mono1.1, Right1#4.16, U1#2.3 (OUT)
Board_5-/9V: J2#2.1, J3#4.1, U1#2.1 (IN)
Board_5-/Control: J1#4.1, LGate1#6.1, RLed1#6.1
Board_5-/Ctrl_GND: D1#2.1 (K), J2#2.2, J3#4.2, LeftPD1#2.2, QL1#4.1 (S), U1#2.2 (GND)
Board_5-/L_Return: J4#6.4, Left/Mono1.8
Board_5-/L_Send: J5#6.1, Left/Mono1.9
Board_5-/L_in: In1#2.2, Left/Mono1.13
Board_5-/L_out: Left/Mono1.4, Out1#4.2
Board_5-/R_Return: J4#6.2, Right1#4.8
Board_5-/R_in: In1#2.3, Right1#4.13
Board_5-/R_out: Out1#4.3, Right1#4.4
Board_5-/R_send: J5#6.3, Right1#4.9
Board_5-/Signal_Gnd: In1#2.1, J4#6.1, J4#6.3, J5#6.2, J5#6.4, Out1#4.1
Board_5-Net-(D1-A): D1#2.2 (A), RLed1#6.2
Board_5-Net-(Left/Mono1-Pad11): Left/Mono1.6, Left/Mono1.11
Board_5-Net-(QL1-D): Left/Mono1.16, QL1#4.3 (D), Right1#4.1
Board_5-Net-(QL1-G): LGate1#6.2, LeftPD1#2.1, QL1#4.2 (G)
Board_5-Net-(Right1-Pad11): Right1#4.6, Right1#4.11
